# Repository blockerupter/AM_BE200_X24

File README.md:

AM_BE200_X24
============

BE200 Board with 24 chips

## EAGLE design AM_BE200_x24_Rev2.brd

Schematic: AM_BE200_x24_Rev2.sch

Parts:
C1, C17, C33, C49, C65, C81, C97, C113: 100uF; 153CLV-0605
C2, C3, C4, C5, C18, C19, C20, C21, C34, C35, C36, C37, C50, C51, C52, C53, C66, C67, C68, C69, C82, C83, C84, C85, C98, C99, C100, C101, C114, C115, C116, C117: 22uF; C1210K
C6, C7, C22, C23, C38, C39, C54, C55, C70, C71, C86, C87, C102, C103, C118, C119: 4.7uF; C0805K
C8, C24, C40, C56, C72, C88, C104, C120: 1nF; C0805K
C9, C25, C41, C57, C73, C89, C105, C121: 22nF; C0805K
C10, C26, C42, C58, C74, C90, C106, C122, C305, C306, C308, C311, C312, C313, C314, C315: 100nF; C0805K
C11, C27, C43, C59, C75, C91, C107, C123, C298: 2,2nF; C0805K
C12, C13, C14, C15, C16, C28, C29, C30, C31, C32, C44, C45, C46, C47, C48, C60, C61, C62, C63, C64, C76, C77, C78, C79, C80, C92, C93, C94, C95, C96, C108, C109, C110, C111, C112, C124, C125, C126, C127, C128: 100uF; C1210K
C129, C130, C131, C132, C134, C136, C137, C138, C139, C141, C143, C144, C145, C146, C148, C150, C151, C152, C153, C155, C157, C158, C159, C160, C162, C164, C165, C166, C167, C169, C171, C172, C173, C174, C176, C178, C179, C180, C181, C183, C185, C186, C187, C188, C190, C192, C193, C194, C195, C197, C199, C200, C201, C202, C204, C206, C207, C208, C209, C211, C213, C214, C215, C216, C218, C220, C221, C222, C223, C225, C227, C228, C229, C230, C232, C234, C235, C236, C237, C239, C241, C242, C243, C244, C246, C248, C249, C250, C251, C253, C255, C256, C257, C258, C260, C262, C263, C264, C265, C267, C269, C270, C271, C272, C274, C276, C277, C278, C279, C281, C283, C284, C285, C286, C288, C290, C291, C292, C293, C295: 100nF; MYRCL_C0603K
C133, C135, C140, C142, C147, C149, C154, C156, C161, C163, C168, C170, C175, C177, C182, C184, C189, C191, C196, C198, C203, C205, C210, C212, C217, C219, C224, C226, C231, C233, C238, C240, C245, C247, C252, C254, C259, C261, C266, C268, C273, C275, C280, C282, C287, C289, C294, C296: 4.7uF; MYRCL_C0603K
C297: 10uF; C1206K
C299, C300: 22uF; C1206K
C301, C302, C303, C304, C307: 4,7uF; C0805K
C309, C310: 22pF; C0805K
C316: 220uF; MYRCL_153CLV-0810
D1: MBR_12V; SMBJ
IC1, IC2, IC3, IC4, IC5, IC6, IC7, IC8: TPS53353_TPS53355_DQP_22; DQP22_5P479X3P24
IC9, IC10, IC11, IC12, IC13, IC14, IC15, IC16, IC17, IC18, IC19, IC20, IC21, IC22, IC23, IC24, IC25, IC26, IC27, IC28, IC29, IC30, IC31, IC32: BE200_QFN64_9X9; QFN64-9X9
IC33: AOZ1021
IC34: TLV71209DBV; SOT-23-5
IC35: TLV7; SOT-23-5
IC36: MEGA88-AU; TQFP32-08
IC37, IC38, IC39, IC40: 74HC138D; SO16
IC41: 7407D; SO14
L1, L2, L3, L4, L5, L6, L7, L8: 0.47uH; INDUCTOR_PA0513
L9: 4.7uH; INDCUCTOR_7.3X7.3
Q1: 20MHZ; OSCILLATOR_7X5_SMD
Q2: 7.37MHZ; HC49UP
R1, R9, R17, R25, R33, R41, R49, R57: 39K; R0805K
R2, R10, R18, R26, R34, R42, R50, R58: 180K; R0805K
R3, R11, R19, R27, R35, R43, R51, R59: 200K; R0805K
R4, R12, R20, R28, R36, R44, R52, R60: 100K; R0805K
R5, R13, R21, R29, R37, R45, R53, R61: 10K; R0805K
R6, R14, R22, R30, R38, R46, R54, R62: 2K49; R0805K
R7, R15, R23, R31, R39, R47, R55, R63: 56K; R0805K
R8, R16, R24, R32, R40, R48, R56, R64: 3 or 3.01; R0805K
R65, R66, R67: 7K5; R0805K
R68: 2K4; R0805K
R69, R70: 4K7; R0805K
S1: 219-05; CTS-219-05
X1, X2: MINI-FIT-JR-065.5MM; PCIE6_4.2
X3: 22-23-2031
X4, X5: XH2.54-3P
X6: AVR-ISP-6VERT; AVR-ISP-6

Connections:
0.9V: C130.1, C137.1, C144.1, C151.1, C158.1, C165.1, C172.1, C179.1, C186.1, C193.1, C200.1, C207.1, C214.1, C221.1, C228.1, C235.1, C242.1, C249.1, C256.1, C263.1, C270.1, C277.1, C284.1, C291.1, C302.2, IC9.8 (PLLDVDD), IC9.10 (PLLVDD), IC10.8 (PLLDVDD), IC10.10 (PLLVDD), IC11.8 (PLLDVDD), IC11.10 (PLLVDD), IC12.8 (PLLDVDD), IC12.10 (PLLVDD), IC13.8 (PLLDVDD), IC13.10 (PLLVDD), IC14.8 (PLLDVDD), IC14.10 (PLLVDD), IC15.8 (PLLDVDD), IC15.10 (PLLVDD), IC16.8 (PLLDVDD), IC16.10 (PLLVDD), IC17.8 (PLLDVDD), IC17.10 (PLLVDD), IC18.8 (PLLDVDD), IC18.10 (PLLVDD), IC19.8 (PLLDVDD), IC19.10 (PLLVDD), IC20.8 (PLLDVDD), IC20.10 (PLLVDD), IC21.8 (PLLDVDD), IC21.10 (PLLVDD), IC22.8 (PLLDVDD), IC22.10 (PLLVDD), IC23.8 (PLLDVDD), IC23.10 (PLLVDD), IC24.8 (PLLDVDD), IC24.10 (PLLVDD), IC25.8 (PLLDVDD), IC25.10 (PLLVDD), IC26.8 (PLLDVDD), IC26.10 (PLLVDD), IC27.8 (PLLDVDD), IC27.10 (PLLVDD), IC28.8 (PLLDVDD), IC28.10 (PLLVDD), IC29.8 (PLLDVDD), IC29.10 (PLLVDD), IC30.8 (PLLDVDD), IC30.10 (PLLVDD), IC31.8 (PLLDVDD), IC31.10 (PLLVDD), IC32.8 (PLLDVDD), IC32.10 (PLLVDD), IC34.5 (OUT)
1.8V: C129.2, C131.1, C136.2, C138.1, C143.2, C145.1, C150.2, C152.1, C157.2, C159.1, C164.2, C166.1, C171.2, C173.1, C178.2, C180.1, C185.2, C187.1, C192.2, C194.1, C199.2, C201.1, C206.2, C208.1, C213.2, C215.1, C220.2, C222.1, C227.2, C229.1, C234.2, C236.1, C241.2, C243.1, C248.2, C250.1, C255.2, C257.1, C262.2, C264.1, C269.2, C271.1, C276.2, C278.1, C283.2, C285.1, C290.2, C292.1, C304.2, IC9.5 (PLLIOVDD), IC9.6 (PLLAHVDD), IC9.25 (VDD_IO), IC9.37 (VDD_IO), IC9.56 (VDD_IO), IC10.5 (PLLIOVDD), IC10.6 (PLLAHVDD), IC10.25 (VDD_IO), IC10.37 (VDD_IO), IC10.56 (VDD_IO), IC11.5 (PLLIOVDD), IC11.6 (PLLAHVDD), IC11.25 (VDD_IO), IC11.37 (VDD_IO), IC11.56 (VDD_IO), IC12.5 (PLLIOVDD), IC12.6 (PLLAHVDD), IC12.25 (VDD_IO), IC12.37 (VDD_IO), IC12.56 (VDD_IO), IC13.5 (PLLIOVDD), IC13.6 (PLLAHVDD), IC13.25 (VDD_IO), IC13.37 (VDD_IO), IC13.56 (VDD_IO), IC14.5 (PLLIOVDD), IC14.6 (PLLAHVDD), IC14.25 (VDD_IO), IC14.37 (VDD_IO), IC14.56 (VDD_IO), IC15.5 (PLLIOVDD), IC15.6 (PLLAHVDD), IC15.25 (VDD_IO), IC15.37 (VDD_IO), IC15.56 (VDD_IO), IC16.5 (PLLIOVDD), IC16.6 (PLLAHVDD), IC16.25 (VDD_IO), IC16.37 (VDD_IO), IC16.56 (VDD_IO), IC17.5 (PLLIOVDD), IC17.6 (PLLAHVDD), IC17.25 (VDD_IO), IC17.37 (VDD_IO), IC17.56 (VDD_IO), IC18.5 (PLLIOVDD), IC18.6 (PLLAHVDD), IC18.25 (VDD_IO), IC18.37 (VDD_IO), IC18.56 (VDD_IO), IC19.5 (PLLIOVDD), IC19.6 (PLLAHVDD), IC19.25 (VDD_IO), IC19.37 (VDD_IO), IC19.56 (VDD_IO), IC20.5 (PLLIOVDD), IC20.6 (PLLAHVDD), IC20.25 (VDD_IO), IC20.37 (VDD_IO), IC20.56 (VDD_IO), IC21.5 (PLLIOVDD), IC21.6 (PLLAHVDD), IC21.25 (VDD_IO), IC21.37 (VDD_IO), IC21.56 (VDD_IO), IC22.5 (PLLIOVDD), IC22.6 (PLLAHVDD), IC22.25 (VDD_IO), IC22.37 (VDD_IO), IC22.56 (VDD_IO), IC23.5 (PLLIOVDD), IC23.6 (PLLAHVDD), IC23.25 (VDD_IO), IC23.37 (VDD_IO), IC23.56 (VDD_IO), IC24.5 (PLLIOVDD), IC24.6 (PLLAHVDD), IC24.25 (VDD_IO), IC24.37 (VDD_IO), IC24.56 (VDD_IO), IC25.5 (PLLIOVDD), IC25.6 (PLLAHVDD), IC25.25 (VDD_IO), IC25.37 (VDD_IO), IC25.56 (VDD_IO), IC26.5 (PLLIOVDD), IC26.6 (PLLAHVDD), IC26.25 (VDD_IO), IC26.37 (VDD_IO), IC26.56 (VDD_IO), IC27.5 (PLLIOVDD), IC27.6 (PLLAHVDD), IC27.25 (VDD_IO), IC27.37 (VDD_IO), IC27.56 (VDD_IO), IC28.5 (PLLIOVDD), IC28.6 (PLLAHVDD), IC28.25 (VDD_IO), IC28.37 (VDD_IO), IC28.56 (VDD_IO)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
+3V3: C299.1, C300.1, C301.2, C303.2, C305.2, C306.2, C307.2, C311.2, C312.2, C313.2, C314.2, C315.2, IC34.1 (IN), IC34.3 (EN), IC35.1 (IN), IC35.3 (EN), IC36.4 (VCC), IC36.6 (VCC), IC36.18 (AVCC), IC37.16 (VCC), IC38.6 (G1), IC38.16 (VCC), IC39.6 (G1), IC39.16 (VCC), IC40.6 (G1), IC40.16 (VCC), IC41.14 (VCC), L9.2, Q1.1 (EN), Q1.4 (VCC), R67.2, R69.2, R70.2, X6.2
+12V: C1.+, C2.1, C3.1, C4.1, C5.1, C7.1, C17.+, C18.1, C19.1, C20.1, C21.1, C23.1, C33.+, C34.1, C35.1, C36.1, C37.1, C39.1, C49.+, C50.1, C51.1, C52.1, C53.1, C55.1, C65.+, C66.1, C67.1, C68.1, C69.1, C71.1, C81.+, C82.1, C83.1, C84.1, C85.1, C87.1, C97.+, C98.1, C99.1, C100.1, C101.1, C103.1, C113.+, C114.1, C115.1, C116.1, C117.1, C119.1, C297.1, C316.+, D1.C, IC1.12 (VIN_2), IC1.13 (VIN_3), IC1.14 (VIN_4), IC1.15 (VIN_5), IC1.16 (VIN_6), IC1.17 (VIN), IC1.19 (VDD), IC2.12 (VIN_2), IC2.13 (VIN_3), IC2.14 (VIN_4), IC2.15 (VIN_5), IC2.16 (VIN_6), IC2.17 (VIN), IC2.19 (VDD), IC3.12 (VIN_2), IC3.13 (VIN_3), IC3.14 (VIN_4), IC3.15 (VIN_5), IC3.16 (VIN_6), IC3.17 (VIN), IC3.19 (VDD), IC4.12 (VIN_2), IC4.13 (VIN_3), IC4.14 (VIN_4), IC4.15 (VIN_5), IC4.16 (VIN_6), IC4.17 (VIN), IC4.19 (VDD), IC5.12 (VIN_2), IC5.13 (VIN_3), IC5.14 (VIN_4), IC5.15 (VIN_5), IC5.16 (VIN_6), IC5.17 (VIN), IC5.19 (VDD), IC6.12 (VIN_2), IC6.13 (VIN_3), IC6.14 (VIN_4), IC6.15 (VIN_5), IC6.16 (VIN_6), IC6.17 (VIN), IC6.19 (VDD), IC7.12 (VIN_2), IC7.13 (VIN_3), IC7.14 (VIN_4), IC7.15 (VIN_5), IC7.16 (VIN_6), IC7.17 (VIN), IC7.19 (VDD), IC8.12 (VIN_2), IC8.13 (VIN_3), IC8.14 (VIN_4), IC8.15 (VIN_5), IC8.16 (VIN_6), IC8.17 (VIN), IC8.19 (VDD), IC33.VIN, R3.2, R11.2, R19.2, R27.2, R35.2, R43.2, R51.2, R59.2, R65.2, X1.P1 (1), X1.P2 (2), X1.P3 (3), X2.P1 (1), X2.P2 (2), X2.P3 (3), X3.2
/CS_EN: IC36.14 (PB2(SS/OC1B/PCINT2)), IC37.4 (G2A), IC37.5 (G2B), R70.1
A0: IC36.23 (PC0(ADC0/PCINT8)), IC38.1 (A), IC39.1 (A), IC40.1 (A)
A1: IC36.24 (PC1(ADC1/PCINT9)), IC38.2 (B), IC39.2 (B), IC40.2 (B)
A2: IC36.25 (PC2(ADC2/PCINT10)), IC38.3 (C), IC39.3 (C), IC40.3 (C)
A3: IC36.26 (PC3(ADC3/PCINT11)), IC37.1 (A)
A4: IC36.27 (PC4(ADC4/SDA/PCINT12)), IC37.2 (B)
BID0: IC36.32 (PD2(INT0/PCINT18)), S1.5
BID1: IC36.1 (PD3(INT1/OC2B/PCINT19)), S1.4
BID2: IC36.2 (PD4(T0/XCK/PCINT20)), S1.3
BID3: IC36.9 (PD5(T1/OC0B/PCINT21)), S1.2
BID4: IC36.10 (PD6(AIN0/OC0A/PCINT22)), S1.1
BS: IC9.13 (BS), IC10.13 (BS), IC11.13 (BS), IC12.13 (BS), IC13.13 (BS), IC14.13 (BS), IC15.13 (BS), IC16.13 (BS), IC17.13 (BS), IC18.13 (BS), IC19.13 (BS), IC20.13 (BS), IC21.13 (BS), IC22.13 (BS), IC23.13 (BS), IC24.13 (BS), IC25.13 (BS), IC26.13 (BS), IC27.13 (BS), IC28.13 (BS), IC29.13 (BS), IC30.13 (BS), IC31.13 (BS), IC32.13 (BS), IC36.11 (PD7(AIN1/PCINT23))
CE0: IC37.15 (Y0), IC38.4 (G2A), IC38.5 (G2B)
CE1: IC37.14 (Y1), IC39.4 (G2A), IC39.5 (G2B)
CE2: IC37.13 (Y2), IC40.4 (G2A), IC40.5 (G2B)
CS0: IC9.39 (/CS_(SS)), IC38.15 (Y0)
CS1: IC10.39 (/CS_(SS)), IC38.14 (Y1)
CS2: IC11.39 (/CS_(SS)), IC38.13 (Y2)
CS3: IC12.39 (/CS_(SS)), IC38.12 (Y3)
CS4: IC13.39 (/CS_(SS)), IC38.11 (Y4)
CS5: IC14.39 (/CS_(SS)), IC38.10 (Y5)
CS6: IC15.39 (/CS_(SS)), IC38.9 (Y6)
CS7: IC16.39 (/CS_(SS)), IC38.7 (Y7)
CS8: IC17.39 (/CS_(SS)), IC39.15 (Y0)
CS9: IC18.39 (/CS_(SS)), IC39.14 (Y1)
CS10: IC19.39 (/CS_(SS)), IC39.13 (Y2)
CS11: IC20.39 (/CS_(SS)), IC39.12 (Y3)
CS12: IC21.39 (/CS_(SS)), IC39.11 (Y4)
CS13: IC22.39 (/CS_(SS)), IC39.10 (Y5)
CS14: IC23.39 (/CS_(SS)), IC39.9 (Y6)
CS15: IC24.39 (/CS_(SS)), IC39.7 (Y7)
CS16: IC25.39 (/CS_(SS)), IC40.15 (Y0)
CS17: IC26.39 (/CS_(SS)), IC40.14 (Y1)
CS18: IC27.39 (/CS_(SS)), IC40.13 (Y2)
CS19: IC28.39 (/CS_(SS)), IC40.12 (Y3)
CS20: IC29.39 (/CS_(SS)), IC40.11 (Y4)
CS21: IC30.39 (/CS_(SS)), IC40.10 (Y5)
CS22: IC31.39 (/CS_(SS)), IC40.9 (Y6)
CS23: IC32.39 (/CS_(SS)), IC40.7 (Y7)
EN_SITE1: IC1.2 (EN), R3.1, R4.2
EN_SITE2: IC2.2 (EN), R11.1, R12.2
EN_SITE3: IC3.2 (EN), R19.1, R20.2
EN_SITE4: IC4.2 (EN), R27.1, R28.2
EN_SITE5: IC5.2 (EN), R35.1, R36.2
EN_SITE6: IC6.2 (EN), R43.1, R44.2
EN_SITE7: IC7.2 (EN), R51.1, R52.2
EN_SITE8: IC8.2 (EN), R59.1, R60.2
GND: C1.-, C2.2, C3.2, C4.2, C5.2, C6.2, C7.2, C11.2, C12.2, C13.2, C14.2, C15.2, C16.2, C17.-, C18.2, C19.2, C20.2, C21.2, C22.2, C23.2, C27.2, C28.2, C29.2, C30.2, C31.2, C32.2, C33.-, C34.2, C35.2, C36.2, C37.2, C38.2, C39.2, C43.2, C44.2, C45.2, C46.2, C47.2, C48.2, C49.-, C50.2, C51.2, C52.2, C53.2, C54.2, C55.2, C59.2, C60.2, C61.2, C62.2, C63.2, C64.2, C65.-, C66.2, C67.2, C68.2, C69.2, C70.2, C71.2, C75.2, C76.2, C77.2, C78.2, C79.2, C80.2, C81.-, C82.2, C83.2, C84.2, C85.2, C86.2, C87.2, C91.2, C92.2, C93.2, C94.2, C95.2, C96.2, C97.-, C98.2, C99.2, C100.2, C101.2, C102.2, C103.2, C107.2, C108.2, C109.2, C110.2, C111.2, C112.2, C113.-, C114.2, C115.2, C116.2, C117.2, C118.2, C119.2, C123.2, C124.2, C125.2, C126.2, C127.2, C128.2, C129.1, C130.2, C131.2, C132.2, C133.2, C134.2, C135.2, C136.1, C137.2, C138.2, C139.2, C140.2, C141.2, C142.2, C143.1, C144.2, C145.2, C146.2, C147.2, C148.2, C149.2, C150.1, C151.2, C152.2, C153.2, C154.2, C155.2, C156.2, C157.1, C158.2, C159.2, C160.2, C161.2, C162.2, C163.2, C164.1, C165.2, C166.2, C167.2, C168.2, C169.2, C170.2, C171.1, C172.2, C173.2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
HARD0: IC9.43 (HARD0), IC10.43 (HARD0), IC11.43 (HARD0), IC12.43 (HARD0), IC13.43 (HARD0), IC14.43 (HARD0), IC15.43 (HARD0), IC16.43 (HARD0), IC17.43 (HARD0), IC18.43 (HARD0), IC19.43 (HARD0), IC20.43 (HARD0), IC21.43 (HARD0), IC22.43 (HARD0), IC23.43 (HARD0), IC24.43 (HARD0), IC25.43 (HARD0), IC26.43 (HARD0), IC27.43 (HARD0), IC28.43 (HARD0), IC29.43 (HARD0), IC30.43 (HARD0), IC31.43 (HARD0), IC32.43 (HARD0), IC36.12 (PB0(ICP1/CLKO/PCINT0))
HARD1: IC9.44 (HARD1), IC10.44 (HARD1), IC11.44 (HARD1), IC12.44 (HARD1), IC13.44 (HARD1), IC14.44 (HARD1), IC15.44 (HARD1), IC16.44 (HARD1), IC17.44 (HARD1), IC18.44 (HARD1), IC19.44 (HARD1), IC20.44 (HARD1), IC21.44 (HARD1), IC22.44 (HARD1), IC23.44 (HARD1), IC24.44 (HARD1), IC25.44 (HARD1), IC26.44 (HARD1), IC27.44 (HARD1), IC28.44 (HARD1), IC29.44 (HARD1), IC30.44 (HARD1), IC31.44 (HARD1), IC32.44 (HARD1), IC36.13 (PB1(OC1A/PCINT1))
MCU_RESET: IC36.29 (PC6(/RESET/PCINT14)), IC37.6 (G1), R69.1, X6.5
MISO_3.3V: IC9.41 (SO), IC10.41 (SO), IC11.41 (SO), IC12.41 (SO), IC13.41 (SO), IC14.41 (SO), IC15.41 (SO), IC16.41 (SO), IC17.41 (SO), IC18.41 (SO), IC19.41 (SO), IC20.41 (SO), IC21.41 (SO), IC22.41 (SO), IC23.41 (SO), IC24.41 (SO), IC25.41 (SO), IC26.41 (SO), IC27.41 (SO), IC28.41 (SO), IC29.41 (SO), IC30.41 (SO), IC31.41 (SO), IC32.41 (SO), IC36.16 (PB4(MISO/PCINT4)), X6.1
MOSI_3.3V: IC9.42 (SI), IC10.42 (SI), IC11.42 (SI), IC12.42 (SI), IC13.42 (SI), IC14.42 (SI), IC15.42 (SI), IC16.42 (SI), IC17.42 (SI), IC18.42 (SI), IC19.42 (SI), IC20.42 (SI), IC21.42 (SI), IC22.42 (SI), IC23.42 (SI), IC24.42 (SI), IC25.42 (SI), IC26.42 (SI), IC27.42 (SI), IC28.42 (SI), IC29.42 (SI), IC30.42 (SI), IC31.42 (SI), IC32.42 (SI), IC36.15 (PB3(MOSI/OC2A/PCINT3)), X6.4
unnamed: C10.2, IC1.6 (LL_2), IC1.7 (LL_3), IC1.8 (LL_4), IC1.9 (LL_5), IC1.10 (LL_6), IC1.11 (LL), L1.2, R7.2, R8.2
unnamed: C11.1, R8.1
unnamed: C8.1, C9.2, R7.1
unnamed: IC1.21 (TRIP), R2.2
unnamed: IC1.20 (MODE), R1.2
unnamed: C6.1, IC1.18 (VREG)
unnamed: C26.2, IC2.6 (LL_2), IC2.7 (LL_3), IC2.8 (LL_4), IC2.9 (LL_5), IC2.10 (LL_6), IC2.11 (LL), L2.2, R15.2, R16.2
unnamed: IC2.21 (TRIP), R10.2
unnamed: C10.1, IC1.4 (VBST)
unnamed: IC2.20 (MODE), R9.2
unnamed: C22.1, IC2.18 (VREG)
unnamed: C26.1, IC2.4 (VBST)
unnamed: C298.1, R66.1
unnamed: C27.1, R16.1
unnamed: C24.1, C25.2, R15.1
unnamed: IC33.LX, L9.1
unnamed: C42.2, IC3.6 (LL_2), IC3.7 (LL_3), IC3.8 (LL_4), IC3.9 (LL_5), IC3.10 (LL_6), IC3.11 (LL), L3.2, R23.2, R24.2
unnamed: IC33.FB, R67.1, R68.2
unnamed: IC33.COMP, R66.2
unnamed: IC33.EN, R65.1
unnamed: C308.2, IC36.20 (AREF)
unnamed: IC3.21 (TRIP), R18.2
unnamed: IC3.20 (MODE), R17.2
unnamed: C38.1, IC3.18 (VREG)
unnamed: C310.1, IC36.7 (PB6(XTAL1/TOSC1/PCINT6)), Q2.2
unnamed: C42.1, IC3.4 (VBST)
unnamed: C43.1, R24.1
unnamed: C309.1, IC36.8 (PB7(XTAL2/TOSC2/PCINT7)), Q2.1
unnamed: C40.1, C41.2, R23.1
unnamed: C58.2, IC4.6 (LL_2), IC4.7 (LL_3), IC4.8 (LL_4), IC4.9 (LL_5), IC4.10 (LL_6), IC4.11 (LL), L4.2, R31.2, R32.2
unnamed: IC4.21 (TRIP), R26.2
unnamed: IC4.20 (MODE), R25.2
unnamed: C54.1, IC4.18 (VREG)
unnamed: C58.1, IC4.4 (VBST)
unnamed: C59.1, R32.1
unnamed: C56.1, C57.2, R31.1
unnamed: C74.2, IC5.6 (LL_2), IC5.7 (LL_3), IC5.8 (LL_4), IC5.9 (LL_5), IC5.10 (LL_6), IC5.11 (LL), L5.2, R39.2, R40.2
unnamed: IC5.21 (TRIP), R34.2
unnamed: IC5.20 (MODE), R33.2
unnamed: C70.1, IC5.18 (VREG)
unnamed: C74.1, IC5.4 (VBST)
unnamed: C75.1, R40.1
unnamed: C72.1, C73.2, R39.1
unnamed: C90.2, IC6.6 (LL_2), IC6.7 (LL_3), IC6.8 (LL_4), IC6.9 (LL_5), IC6.10 (LL_6), IC6.11 (LL), L6.2, R47.2, R48.2
unnamed: IC6.21 (TRIP), R42.2
unnamed: IC6.20 (MODE), R41.2
unnamed: C86.1, IC6.18 (VREG)
unnamed: C90.1, IC6.4 (VBST)
unnamed: C91.1, R48.1
unnamed: C88.1, C89.2, R47.1
unnamed: C106.2, IC7.6 (LL_2), IC7.7 (LL_3), IC7.8 (LL_4), IC7.9 (LL_5), IC7.10 (LL_6), IC7.11 (LL), L7.2, R55.2, R56.2
unnamed: IC7.21 (TRIP), R50.2
unnamed: IC7.20 (MODE), R49.2
unnamed: C102.1, IC7.18 (VREG)
unnamed: C106.1, IC7.4 (VBST)
unnamed: C107.1, R56.1
unnamed: C104.1, C105.2, R55.1
unnamed: C122.2, IC8.6 (LL_2), IC8.7 (LL_3), IC8.8 (LL_4), IC8.9 (LL_5), IC8.10 (LL_6), IC8.11 (LL), L8.2, R63.2, R64.2
unnamed: IC8.21 (TRIP), R58.2
unnamed: IC8.20 (MODE), R57.2
unnamed: C118.1, IC8.18 (VREG)
unnamed: C122.1, IC8.4 (VBST)
unnamed: C123.1, R64.1
unnamed: C120.1, C121.2, R63.1
OSC_CLK: IC9.12 (OSC_CLK), IC10.12 (OSC_CLK), IC11.12 (OSC_CLK), IC12.12 (OSC_CLK), IC13.12 (OSC_CLK), IC14.12 (OSC_CLK), IC15.12 (OSC_CLK), IC16.12 (OSC_CLK), IC17.12 (OSC_CLK), IC18.12 (OSC_CLK), IC19.12 (OSC_CLK), IC20.12 (OSC_CLK), IC21.12 (OSC_CLK), IC22.12 (OSC_CLK), IC23.12 (OSC_CLK), IC24.12 (OSC_CLK), IC25.12 (OSC_CLK), IC26.12 (OSC_CLK), IC27.12 (OSC_CLK), IC28.12 (OSC_CLK), IC29.12 (OSC_CLK), IC30.12 (OSC_CLK), IC31.12 (OSC_CLK), IC32.12 (OSC_CLK), Q1.3 (OUT)
RESET: IC9.38 (RESET), IC10.38 (RESET), IC11.38 (RESET), IC12.38 (RESET), IC13.38 (RESET), IC14.38 (RESET), IC15.38 (RESET), IC16.38 (RESET), IC17.38 (RESET), IC18.38 (RESET), IC19.38 (RESET), IC20.38 (RESET), IC21.38 (RESET), IC22.38 (RESET), IC23.38 (RESET), IC24.38 (RESET), IC25.38 (RESET), IC26.38 (RESET), IC27.38 (RESET), IC28.38 (RESET), IC29.38 (RESET), IC30.38 (RESET), IC31.38 (RESET), IC32.38 (RESET), IC36.28 (PC5(ADC5/SCL/PCINT13))
RXD: IC36.30 (PD0(RXD/PCINT16)), X4.1, X5.1
SCK_3.3V: IC9.40 (SCK), IC10.40 (SCK), IC11.40 (SCK), IC12.40 (SCK), IC13.40 (SCK), IC14.40 (SCK), IC15.40 (SCK), IC16.40 (SCK), IC17.40 (SCK), IC18.40 (SCK), IC19.40 (SCK), IC20.40 (SCK), IC21.40 (SCK), IC22.40 (SCK), IC23.40 (SCK), IC24.40 (SCK), IC25.40 (SCK), IC26.40 (SCK), IC27.40 (SCK), IC28.40 (SCK), IC29.40 (SCK), IC30.40 (SCK), IC31.40 (SCK), IC32.40 (SCK), IC36.17 (PB5(SCK/PCINT5)), X6.3
TXD: IC41.2 (O), IC41.4 (O), IC41.6 (O), IC41.8 (O), IC41.10 (O), IC41.12 (O), X4.2, X5.2
TXD_MCU: IC36.31 (PD1(TXD/PCINT17)), IC41.1 (I), IC41.3 (I), IC41.5 (I), IC41.9 (I), IC41.11 (I), IC41.13 (I)
VCORE_SITE1: C9.1, C12.1, C13.1, C14.1, C15.1, C16.1, C132.1, C133.1, C134.1, C135.1, C139.1, C140.1, C141.1, C142.1, C146.1, C147.1, C148.1, C149.1, IC9.1 (VDD_CORE), IC9.2 (VDD_CORE), IC9.3 (VDD_CORE), IC9.4 (VDD_CORE), IC9.14 (VDD_CORE), IC9.15 (VDD_CORE), IC9.16 (VDD_CORE), IC9.17 (VDD_CORE), IC9.18 (VDD_CORE), IC9.19 (VDD_CORE), IC9.20 (VDD_CORE), IC9.21 (VDD_CORE), IC9.22 (VDD_CORE), IC9.23 (VDD_CORE), IC9.24 (VDD_CORE), IC9.26 (VDD_CORE), IC9.27 (VDD_CORE), IC9.28 (VDD_CORE), IC9.29 (VDD_CORE), IC9.30 (VDD_CORE), IC9.31 (VDD_CORE), IC9.32 (VDD_CORE), IC9.33 (VDD_CORE), IC9.34 (VDD_CORE), IC9.35 (VDD_CORE), IC9.36 (VDD_CORE), IC9.45 (VDD_CORE), IC9.46 (VDD_CORE), IC9.47 (VDD_CORE), IC9.48 (VDD_CORE), IC9.49 (VDD_CORE), IC9.50 (VDD_CORE), IC9.51 (VDD_CORE), IC9.52 (VDD_CORE), IC9.53 (VDD_CORE), IC9.54 (VDD_CORE), IC9.55 (VDD_CORE), IC9.57 (VDD_CORE), IC9.58 (VDD_CORE), IC9.59 (VDD_CORE), IC9.60 (VDD_CORE), IC9.61 (VDD_CORE), IC9.62 (VDD_CORE), IC9.63 (VDD_CORE), IC9.64 (VDD_CORE), IC10.1 (VDD_CORE), IC10.2 (VDD_CORE), IC10.3 (VDD_CORE), IC10.4 (VDD_CORE), IC10.14 (VDD_CORE), IC10.15 (VDD_CORE), IC10.16 (VDD_CORE), IC10.17 (VDD_CORE), IC10.18 (VDD_CORE), IC10.19 (VDD_CORE), IC10.20 (VDD_CORE), IC10.21 (VDD_CORE), IC10.22 (VDD_CORE), IC10.23 (VDD_CORE), IC10.24 (VDD_CORE), IC10.26 (VDD_CORE), IC10.27 (VDD_CORE), IC10.28 (VDD_CORE), IC10.29 (VDD_CORE), IC10.30 (VDD_CORE), IC10.31 (VDD_CORE), IC10.32 (VDD_CORE), IC10.33 (VDD_CORE), IC10.34 (VDD_CORE), IC10.35 (VDD_CORE), IC10.36 (VDD_CORE), IC10.45 (VDD_CORE), IC10.46 (VDD_CORE), IC10.47 (VDD_CORE), IC10.48 (VDD_CORE), IC10.49 (VDD_CORE), IC10.50 (VDD_CORE), IC10.51 (VDD_CORE), IC10.52 (VDD_CORE), IC10.53 (VDD_CORE), IC10.54 (VDD_CORE), IC10.55 (VDD_CORE), IC10.57 (VDD_CORE), IC10.58 (VDD_CORE), IC10.59 (VDD_CORE), IC10.60 (VDD_CORE), IC10.61 (VDD_CORE), IC10.62 (VDD_CORE), IC10.63 (VDD_CORE), IC10.64 (VDD_CORE), IC11.1 (VDD_CORE), IC11.2 (VDD_CORE), IC11.3 (VDD_CORE), IC11.4 (VDD_CORE), IC11.14 (VDD_CORE), IC11.15 (VDD_CORE), IC11.16 (VDD_CORE), IC11.17 (VDD_CORE), IC11.18 (VDD_CORE), IC11.19 (VDD_CORE), IC11.20 (VDD_CORE), IC11.21 (VDD_CORE), IC11.22 (VDD_CORE), IC11.23 (VDD_CORE), IC11.24 (VDD_CORE), IC11.26 (VDD_CORE), IC11.27 (VDD_CORE), IC11.28 (VDD_CORE), IC11.29 (VDD_CORE), IC11.30 (VDD_CORE), IC11.31 (VDD_CORE), IC11.32 (VDD_CORE), IC11.33 (VDD_CORE), IC11.34 (VDD_CORE), IC11.35 (VDD_CORE), IC11.36 (VDD_CORE), IC11.45 (VDD_CORE), IC11.46 (VDD_CORE), IC11.47 (VDD_CORE), IC11.48 (VDD_CORE), IC11.49 (VDD_CORE), IC11.50 (VDD_CORE), IC11.51 (VDD_CORE), IC11.52 (VDD_CORE), IC11.53 (VDD_CORE), IC11.54 (VDD_CORE), IC11.55 (VDD_CORE), IC11.57 (VDD_CORE), IC11.58 (VDD_CORE), IC11.59 (VDD_CORE), IC11.60 (VDD_CORE)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
VCORE_SITE2: C25.1, C28.1, C29.1, C30.1, C31.1, C32.1, C153.1, C154.1, C155.1, C156.1, C160.1, C161.1, C162.1, C163.1, C167.1, C168.1, C169.1, C170.1, IC12.1 (VDD_CORE), IC12.2 (VDD_CORE), IC12.3 (VDD_CORE), IC12.4 (VDD_CORE), IC12.14 (VDD_CORE), IC12.15 (VDD_CORE), IC12.16 (VDD_CORE), IC12.17 (VDD_CORE), IC12.18 (VDD_CORE), IC12.19 (VDD_CORE), IC12.20 (VDD_CORE), IC12.21 (VDD_CORE), IC12.22 (VDD_CORE), IC12.23 (VDD_CORE), IC12.24 (VDD_CORE), IC12.26 (VDD_CORE), IC12.27 (VDD_CORE), IC12.28 (VDD_CORE), IC12.29 (VDD_CORE), IC12.30 (VDD_CORE), IC12.31 (VDD_CORE), IC12.32 (VDD_CORE), IC12.33 (VDD_CORE), IC12.34 (VDD_CORE), IC12.35 (VDD_CORE), IC12.36 (VDD_CORE), IC12.45 (VDD_CORE), IC12.46 (VDD_CORE), IC12.47 (VDD_CORE), IC12.48 (VDD_CORE), IC12.49 (VDD_CORE), IC12.50 (VDD_CORE), IC12.51 (VDD_CORE), IC12.52 (VDD_CORE), IC12.53 (VDD_CORE), IC12.54 (VDD_CORE), IC12.55 (VDD_CORE), IC12.57 (VDD_CORE), IC12.58 (VDD_CORE), IC12.59 (VDD_CORE), IC12.60 (VDD_CORE), IC12.61 (VDD_CORE), IC12.62 (VDD_CORE), IC12.63 (VDD_CORE), IC12.64 (VDD_CORE), IC13.1 (VDD_CORE), IC13.2 (VDD_CORE), IC13.3 (VDD_CORE), IC13.4 (VDD_CORE), IC13.14 (VDD_CORE), IC13.15 (VDD_CORE), IC13.16 (VDD_CORE), IC13.17 (VDD_CORE), IC13.18 (VDD_CORE), IC13.19 (VDD_CORE), IC13.20 (VDD_CORE), IC13.21 (VDD_CORE), IC13.22 (VDD_CORE), IC13.23 (VDD_CORE), IC13.24 (VDD_CORE), IC13.26 (VDD_CORE), IC13.27 (VDD_CORE), IC13.28 (VDD_CORE), IC13.29 (VDD_CORE), IC13.30 (VDD_CORE), IC13.31 (VDD_CORE), IC13.32 (VDD_CORE), IC13.33 (VDD_CORE), IC13.34 (VDD_CORE), IC13.35 (VDD_CORE), IC13.36 (VDD_CORE), IC13.45 (VDD_CORE), IC13.46 (VDD_CORE), IC13.47 (VDD_CORE), IC13.48 (VDD_CORE), IC13.49 (VDD_CORE), IC13.50 (VDD_CORE), IC13.51 (VDD_CORE), IC13.52 (VDD_CORE), IC13.53 (VDD_CORE), IC13.54 (VDD_CORE), IC13.55 (VDD_CORE), IC13.57 (VDD_CORE), IC13.58 (VDD_CORE), IC13.59 (VDD_CORE), IC13.60 (VDD_CORE), IC13.61 (VDD_CORE), IC13.62 (VDD_CORE), IC13.63 (VDD_CORE), IC13.64 (VDD_CORE), IC14.1 (VDD_CORE), IC14.2 (VDD_CORE), IC14.3 (VDD_CORE), IC14.4 (VDD_CORE), IC14.14 (VDD_CORE), IC14.15 (VDD_CORE), IC14.16 (VDD_CORE), IC14.17 (VDD_CORE), IC14.18 (VDD_CORE), IC14.19 (VDD_CORE), IC14.20 (VDD_CORE), IC14.21 (VDD_CORE), IC14.22 (VDD_CORE), IC14.23 (VDD_CORE), IC14.24 (VDD_CORE), IC14.26 (VDD_CORE), IC14.27 (VDD_CORE), IC14.28 (VDD_CORE), IC14.29 (VDD_CORE), IC14.30 (VDD_CORE), IC14.31 (VDD_CORE), IC14.32 (VDD_CORE), IC14.33 (VDD_CORE), IC14.34 (VDD_CORE), IC14.35 (VDD_CORE), IC14.36 (VDD_CORE), IC14.45 (VDD_CORE), IC14.46 (VDD_CORE), IC14.47 (VDD_CORE), IC14.48 (VDD_CORE), IC14.49 (VDD_CORE), IC14.50 (VDD_CORE), IC14.51 (VDD_CORE), IC14.52 (VDD_CORE), IC14.53 (VDD_CORE), IC14.54 (VDD_CORE), IC14.55 (VDD_CORE), IC14.57 (VDD_CORE), IC14.58 (VDD_CORE), IC14.59 (VDD_CORE), IC14.60 (VDD_CORE)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
VCORE_SITE3: C41.1, C44.1, C45.1, C46.1, C47.1, C48.1, C174.1, C175.1, C176.1, C177.1, C181.1, C182.1, C183.1, C184.1, C188.1, C189.1, C190.1, C191.1, IC15.1 (VDD_CORE), IC15.2 (VDD_CORE), IC15.3 (VDD_CORE), IC15.4 (VDD_CORE), IC15.14 (VDD_CORE), IC15.15 (VDD_CORE), IC15.16 (VDD_CORE), IC15.17 (VDD_CORE), IC15.18 (VDD_CORE), IC15.19 (VDD_CORE), IC15.20 (VDD_CORE), IC15.21 (VDD_CORE), IC15.22 (VDD_CORE), IC15.23 (VDD_CORE), IC15.24 (VDD_CORE), IC15.26 (VDD_CORE), IC15.27 (VDD_CORE), IC15.28 (VDD_CORE), IC15.29 (VDD_CORE), IC15.30 (VDD_CORE), IC15.31 (VDD_CORE), IC15.32 (VDD_CORE), IC15.33 (VDD_CORE), IC15.34 (VDD_CORE), IC15.35 (VDD_CORE), IC15.36 (VDD_CORE), IC15.45 (VDD_CORE), IC15.46 (VDD_CORE), IC15.47 (VDD_CORE), IC15.48 (VDD_CORE), IC15.49 (VDD_CORE), IC15.50 (VDD_CORE), IC15.51 (VDD_CORE), IC15.52 (VDD_CORE), IC15.53 (VDD_CORE), IC15.54 (VDD_CORE), IC15.55 (VDD_CORE), IC15.57 (VDD_CORE), IC15.58 (VDD_CORE), IC15.59 (VDD_CORE), IC15.60 (VDD_CORE), IC15.61 (VDD_CORE), IC15.62 (VDD_CORE), IC15.63 (VDD_CORE), IC15.64 (VDD_CORE), IC16.1 (VDD_CORE), IC16.2 (VDD_CORE), IC16.3 (VDD_CORE), IC16.4 (VDD_CORE), IC16.14 (VDD_CORE), IC16.15 (VDD_CORE), IC16.16 (VDD_CORE), IC16.17 (VDD_CORE), IC16.18 (VDD_CORE), IC16.19 (VDD_CORE), IC16.20 (VDD_CORE), IC16.21 (VDD_CORE), IC16.22 (VDD_CORE), IC16.23 (VDD_CORE), IC16.24 (VDD_CORE), IC16.26 (VDD_CORE), IC16.27 (VDD_CORE), IC16.28 (VDD_CORE), IC16.29 (VDD_CORE), IC16.30 (VDD_CORE), IC16.31 (VDD_CORE), IC16.32 (VDD_CORE), IC16.33 (VDD_CORE), IC16.34 (VDD_CORE), IC16.35 (VDD_CORE), IC16.36 (VDD_CORE), IC16.45 (VDD_CORE), IC16.46 (VDD_CORE), IC16.47 (VDD_CORE), IC16.48 (VDD_CORE), IC16.49 (VDD_CORE), IC16.50 (VDD_CORE), IC16.51 (VDD_CORE), IC16.52 (VDD_CORE), IC16.53 (VDD_CORE), IC16.54 (VDD_CORE), IC16.55 (VDD_CORE), IC16.57 (VDD_CORE), IC16.58 (VDD_CORE), IC16.59 (VDD_CORE), IC16.60 (VDD_CORE), IC16.61 (VDD_CORE), IC16.62 (VDD_CORE), IC16.63 (VDD_CORE), IC16.64 (VDD_CORE), IC17.1 (VDD_CORE), IC17.2 (VDD_CORE), IC17.3 (VDD_CORE), IC17.4 (VDD_CORE), IC17.14 (VDD_CORE), IC17.15 (VDD_CORE), IC17.16 (VDD_CORE), IC17.17 (VDD_CORE), IC17.18 (VDD_CORE), IC17.19 (VDD_CORE), IC17.20 (VDD_CORE), IC17.21 (VDD_CORE), IC17.22 (VDD_CORE), IC17.23 (VDD_CORE), IC17.24 (VDD_CORE), IC17.26 (VDD_CORE), IC17.27 (VDD_CORE), IC17.28 (VDD_CORE), IC17.29 (VDD_CORE), IC17.30 (VDD_CORE), IC17.31 (VDD_CORE), IC17.32 (VDD_CORE), IC17.33 (VDD_CORE), IC17.34 (VDD_CORE), IC17.35 (VDD_CORE), IC17.36 (VDD_CORE), IC17.45 (VDD_CORE), IC17.46 (VDD_CORE), IC17.47 (VDD_CORE), IC17.48 (VDD_CORE), IC17.49 (VDD_CORE), IC17.50 (VDD_CORE), IC17.51 (VDD_CORE), IC17.52 (VDD_CORE), IC17.53 (VDD_CORE), IC17.54 (VDD_CORE), IC17.55 (VDD_CORE), IC17.57 (VDD_CORE), IC17.58 (VDD_CORE), IC17.59 (VDD_CORE), IC17.60 (VDD_CORE)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
VCORE_SITE4: C57.1, C60.1, C61.1, C62.1, C63.1, C64.1, C195.1, C196.1, C197.1, C198.1, C202.1, C203.1, C204.1, C205.1, C209.1, C210.1, C211.1, C212.1, IC18.1 (VDD_CORE), IC18.2 (VDD_CORE), IC18.3 (VDD_CORE), IC18.4 (VDD_CORE), IC18.14 (VDD_CORE), IC18.15 (VDD_CORE), IC18.16 (VDD_CORE), IC18.17 (VDD_CORE), IC18.18 (VDD_CORE), IC18.19 (VDD_CORE), IC18.20 (VDD_CORE), IC18.21 (VDD_CORE), IC18.22 (VDD_CORE), IC18.23 (VDD_CORE), IC18.24 (VDD_CORE), IC18.26 (VDD_CORE), IC18.27 (VDD_CORE), IC18.28 (VDD_CORE), IC18.29 (VDD_CORE), IC18.30 (VDD_CORE), IC18.31 (VDD_CORE), IC18.32 (VDD_CORE), IC18.33 (VDD_CORE), IC18.34 (VDD_CORE), IC18.35 (VDD_CORE), IC18.36 (VDD_CORE), IC18.45 (VDD_CORE), IC18.46 (VDD_CORE), IC18.47 (VDD_CORE), IC18.48 (VDD_CORE), IC18.49 (VDD_CORE), IC18.50 (VDD_CORE), IC18.51 (VDD_CORE), IC18.52 (VDD_CORE), IC18.53 (VDD_CORE), IC18.54 (VDD_CORE), IC18.55 (VDD_CORE), IC18.57 (VDD_CORE), IC18.58 (VDD_CORE), IC18.59 (VDD_CORE), IC18.60 (VDD_CORE), IC18.61 (VDD_CORE), IC18.62 (VDD_CORE), IC18.63 (VDD_CORE), IC18.64 (VDD_CORE), IC19.1 (VDD_CORE), IC19.2 (VDD_CORE), IC19.3 (VDD_CORE), IC19.4 (VDD_CORE), IC19.14 (VDD_CORE), IC19.15 (VDD_CORE), IC19.16 (VDD_CORE), IC19.17 (VDD_CORE), IC19.18 (VDD_CORE), IC19.19 (VDD_CORE), IC19.20 (VDD_CORE), IC19.21 (VDD_CORE), IC19.22 (VDD_CORE), IC19.23 (VDD_CORE), IC19.24 (VDD_CORE), IC19.26 (VDD_CORE), IC19.27 (VDD_CORE), IC19.28 (VDD_CORE), IC19.29 (VDD_CORE), IC19.30 (VDD_CORE), IC19.31 (VDD_CORE), IC19.32 (VDD_CORE), IC19.33 (VDD_CORE), IC19.34 (VDD_CORE), IC19.35 (VDD_CORE), IC19.36 (VDD_CORE), IC19.45 (VDD_CORE), IC19.46 (VDD_CORE), IC19.47 (VDD_CORE), IC19.48 (VDD_CORE), IC19.49 (VDD_CORE), IC19.50 (VDD_CORE), IC19.51 (VDD_CORE), IC19.52 (VDD_CORE), IC19.53 (VDD_CORE), IC19.54 (VDD_CORE), IC19.55 (VDD_CORE), IC19.57 (VDD_CORE), IC19.58 (VDD_CORE), IC19.59 (VDD_CORE), IC19.60 (VDD_CORE), IC19.61 (VDD_CORE), IC19.62 (VDD_CORE), IC19.63 (VDD_CORE), IC19.64 (VDD_CORE), IC20.1 (VDD_CORE), IC20.2 (VDD_CORE), IC20.3 (VDD_CORE), IC20.4 (VDD_CORE), IC20.14 (VDD_CORE), IC20.15 (VDD_CORE), IC20.16 (VDD_CORE), IC20.17 (VDD_CORE), IC20.18 (VDD_CORE), IC20.19 (VDD_CORE), IC20.20 (VDD_CORE), IC20.21 (VDD_CORE), IC20.22 (VDD_CORE), IC20.23 (VDD_CORE), IC20.24 (VDD_CORE), IC20.26 (VDD_CORE), IC20.27 (VDD_CORE), IC20.28 (VDD_CORE), IC20.29 (VDD_CORE), IC20.30 (VDD_CORE), IC20.31 (VDD_CORE), IC20.32 (VDD_CORE), IC20.33 (VDD_CORE), IC20.34 (VDD_CORE), IC20.35 (VDD_CORE), IC20.36 (VDD_CORE), IC20.45 (VDD_CORE), IC20.46 (VDD_CORE), IC20.47 (VDD_CORE), IC20.48 (VDD_CORE), IC20.49 (VDD_CORE), IC20.50 (VDD_CORE), IC20.51 (VDD_CORE), IC20.52 (VDD_CORE), IC20.53 (VDD_CORE), IC20.54 (VDD_CORE), IC20.55 (VDD_CORE), IC20.57 (VDD_CORE), IC20.58 (VDD_CORE), IC20.59 (VDD_CORE), IC20.60 (VDD_CORE)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
VCORE_SITE5: C73.1, C76.1, C77.1, C78.1, C79.1, C80.1, C216.1, C217.1, C218.1, C219.1, C223.1, C224.1, C225.1, C226.1, C230.1, C231.1, C232.1, C233.1, IC21.1 (VDD_CORE), IC21.2 (VDD_CORE), IC21.3 (VDD_CORE), IC21.4 (VDD_CORE), IC21.14 (VDD_CORE), IC21.15 (VDD_CORE), IC21.16 (VDD_CORE), IC21.17 (VDD_CORE), IC21.18 (VDD_CORE), IC21.19 (VDD_CORE), IC21.20 (VDD_CORE), IC21.21 (VDD_CORE), IC21.22 (VDD_CORE), IC21.23 (VDD_CORE), IC21.24 (VDD_CORE), IC21.26 (VDD_CORE), IC21.27 (VDD_CORE), IC21.28 (VDD_CORE), IC21.29 (VDD_CORE), IC21.30 (VDD_CORE), IC21.31 (VDD_CORE), IC21.32 (VDD_CORE), IC21.33 (VDD_CORE), IC21.34 (VDD_CORE), IC21.35 (VDD_CORE), IC21.36 (VDD_CORE), IC21.45 (VDD_CORE), IC21.46 (VDD_CORE), IC21.47 (VDD_CORE), IC21.48 (VDD_CORE), IC21.49 (VDD_CORE), IC21.50 (VDD_CORE), IC21.51 (VDD_CORE), IC21.52 (VDD_CORE), IC21.53 (VDD_CORE), IC21.54 (VDD_CORE), IC21.55 (VDD_CORE), IC21.57 (VDD_CORE), IC21.58 (VDD_CORE), IC21.59 (VDD_CORE), IC21.60 (VDD_CORE), IC21.61 (VDD_CORE), IC21.62 (VDD_CORE), IC21.63 (VDD_CORE), IC21.64 (VDD_CORE), IC22.1 (VDD_CORE), IC22.2 (VDD_CORE), IC22.3 (VDD_CORE), IC22.4 (VDD_CORE), IC22.14 (VDD_CORE), IC22.15 (VDD_CORE), IC22.16 (VDD_CORE), IC22.17 (VDD_CORE), IC22.18 (VDD_CORE), IC22.19 (VDD_CORE), IC22.20 (VDD_CORE), IC22.21 (VDD_CORE), IC22.22 (VDD_CORE), IC22.23 (VDD_CORE), IC22.24 (VDD_CORE), IC22.26 (VDD_CORE), IC22.27 (VDD_CORE), IC22.28 (VDD_CORE), IC22.29 (VDD_CORE), IC22.30 (VDD_CORE), IC22.31 (VDD_CORE), IC22.32 (VDD_CORE), IC22.33 (VDD_CORE), IC22.34 (VDD_CORE), IC22.35 (VDD_CORE), IC22.36 (VDD_CORE), IC22.45 (VDD_CORE), IC22.46 (VDD_CORE), IC22.47 (VDD_CORE), IC22.48 (VDD_CORE), IC22.49 (VDD_CORE), IC22.50 (VDD_CORE), IC22.51 (VDD_CORE), IC22.52 (VDD_CORE), IC22.53 (VDD_CORE), IC22.54 (VDD_CORE), IC22.55 (VDD_CORE), IC22.57 (VDD_CORE), IC22.58 (VDD_CORE), IC22.59 (VDD_CORE), IC22.60 (VDD_CORE), IC22.61 (VDD_CORE), IC22.62 (VDD_CORE), IC22.63 (VDD_CORE), IC22.64 (VDD_CORE), IC23.1 (VDD_CORE), IC23.2 (VDD_CORE), IC23.3 (VDD_CORE), IC23.4 (VDD_CORE), IC23.14 (VDD_CORE), IC23.15 (VDD_CORE), IC23.16 (VDD_CORE), IC23.17 (VDD_CORE), IC23.18 (VDD_CORE), IC23.19 (VDD_CORE), IC23.20 (VDD_CORE), IC23.21 (VDD_CORE), IC23.22 (VDD_CORE), IC23.23 (VDD_CORE), IC23.24 (VDD_CORE), IC23.26 (VDD_CORE), IC23.27 (VDD_CORE), IC23.28 (VDD_CORE), IC23.29 (VDD_CORE), IC23.30 (VDD_CORE), IC23.31 (VDD_CORE), IC23.32 (VDD_CORE), IC23.33 (VDD_CORE), IC23.34 (VDD_CORE), IC23.35 (VDD_CORE), IC23.36 (VDD_CORE), IC23.45 (VDD_CORE), IC23.46 (VDD_CORE), IC23.47 (VDD_CORE), IC23.48 (VDD_CORE), IC23.49 (VDD_CORE), IC23.50 (VDD_CORE), IC23.51 (VDD_CORE), IC23.52 (VDD_CORE), IC23.53 (VDD_CORE), IC23.54 (VDD_CORE), IC23.55 (VDD_CORE), IC23.57 (VDD_CORE), IC23.58 (VDD_CORE), IC23.59 (VDD_CORE), IC23.60 (VDD_CORE)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
VCORE_SITE6: C89.1, C92.1, C93.1, C94.1, C95.1, C96.1, C237.1, C238.1, C239.1, C240.1, C244.1, C245.1, C246.1, C247.1, C251.1, C252.1, C253.1, C254.1, IC24.1 (VDD_CORE), IC24.2 (VDD_CORE), IC24.3 (VDD_CORE), IC24.4 (VDD_CORE), IC24.14 (VDD_CORE), IC24.15 (VDD_CORE), IC24.16 (VDD_CORE), IC24.17 (VDD_CORE), IC24.18 (VDD_CORE), IC24.19 (VDD_CORE), IC24.20 (VDD_CORE), IC24.21 (VDD_CORE), IC24.22 (VDD_CORE), IC24.23 (VDD_CORE), IC24.24 (VDD_CORE), IC24.26 (VDD_CORE), IC24.27 (VDD_CORE), IC24.28 (VDD_CORE), IC24.29 (VDD_CORE), IC24.30 (VDD_CORE), IC24.31 (VDD_CORE), IC24.32 (VDD_CORE), IC24.33 (VDD_CORE), IC24.34 (VDD_CORE), IC24.35 (VDD_CORE), IC24.36 (VDD_CORE), IC24.45 (VDD_CORE), IC24.46 (VDD_CORE), IC24.47 (VDD_CORE), IC24.48 (VDD_CORE), IC24.49 (VDD_CORE), IC24.50 (VDD_CORE), IC24.51 (VDD_CORE), IC24.52 (VDD_CORE), IC24.53 (VDD_CORE), IC24.54 (VDD_CORE), IC24.55 (VDD_CORE), IC24.57 (VDD_CORE), IC24.58 (VDD_CORE), IC24.59 (VDD_CORE), IC24.60 (VDD_CORE), IC24.61 (VDD_CORE), IC24.62 (VDD_CORE), IC24.63 (VDD_CORE), IC24.64 (VDD_CORE), IC25.1 (VDD_CORE), IC25.2 (VDD_CORE), IC25.3 (VDD_CORE), IC25.4 (VDD_CORE), IC25.14 (VDD_CORE), IC25.15 (VDD_CORE), IC25.16 (VDD_CORE), IC25.17 (VDD_CORE), IC25.18 (VDD_CORE), IC25.19 (VDD_CORE), IC25.20 (VDD_CORE), IC25.21 (VDD_CORE), IC25.22 (VDD_CORE), IC25.23 (VDD_CORE), IC25.24 (VDD_CORE), IC25.26 (VDD_CORE), IC25.27 (VDD_CORE), IC25.28 (VDD_CORE), IC25.29 (VDD_CORE), IC25.30 (VDD_CORE), IC25.31 (VDD_CORE), IC25.32 (VDD_CORE), IC25.33 (VDD_CORE), IC25.34 (VDD_CORE), IC25.35 (VDD_CORE), IC25.36 (VDD_CORE), IC25.45 (VDD_CORE), IC25.46 (VDD_CORE), IC25.47 (VDD_CORE), IC25.48 (VDD_CORE), IC25.49 (VDD_CORE), IC25.50 (VDD_CORE), IC25.51 (VDD_CORE), IC25.52 (VDD_CORE), IC25.53 (VDD_CORE), IC25.54 (VDD_CORE), IC25.55 (VDD_CORE), IC25.57 (VDD_CORE), IC25.58 (VDD_CORE), IC25.59 (VDD_CORE), IC25.60 (VDD_CORE), IC25.61 (VDD_CORE), IC25.62 (VDD_CORE), IC25.63 (VDD_CORE), IC25.64 (VDD_CORE), IC26.1 (VDD_CORE), IC26.2 (VDD_CORE), IC26.3 (VDD_CORE), IC26.4 (VDD_CORE), IC26.14 (VDD_CORE), IC26.15 (VDD_CORE), IC26.16 (VDD_CORE), IC26.17 (VDD_CORE), IC26.18 (VDD_CORE), IC26.19 (VDD_CORE), IC26.20 (VDD_CORE), IC26.21 (VDD_CORE), IC26.22 (VDD_CORE), IC26.23 (VDD_CORE), IC26.24 (VDD_CORE), IC26.26 (VDD_CORE), IC26.27 (VDD_CORE), IC26.28 (VDD_CORE), IC26.29 (VDD_CORE), IC26.30 (VDD_CORE), IC26.31 (VDD_CORE), IC26.32 (VDD_CORE), IC26.33 (VDD_CORE), IC26.34 (VDD_CORE), IC26.35 (VDD_CORE), IC26.36 (VDD_CORE), IC26.45 (VDD_CORE), IC26.46 (VDD_CORE), IC26.47 (VDD_CORE), IC26.48 (VDD_CORE), IC26.49 (VDD_CORE), IC26.50 (VDD_CORE), IC26.51 (VDD_CORE), IC26.52 (VDD_CORE), IC26.53 (VDD_CORE), IC26.54 (VDD_CORE), IC26.55 (VDD_CORE), IC26.57 (VDD_CORE), IC26.58 (VDD_CORE), IC26.59 (VDD_CORE), IC26.60 (VDD_CORE)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
VCORE_SITE7: C105.1, C108.1, C109.1, C110.1, C111.1, C112.1, C258.1, C259.1, C260.1, C261.1, C265.1, C266.1, C267.1, C268.1, C272.1, C273.1, C274.1, C275.1, IC27.1 (VDD_CORE), IC27.2 (VDD_CORE), IC27.3 (VDD_CORE), IC27.4 (VDD_CORE), IC27.14 (VDD_CORE), IC27.15 (VDD_CORE), IC27.16 (VDD_CORE), IC27.17 (VDD_CORE), IC27.18 (VDD_CORE), IC27.19 (VDD_CORE), IC27.20 (VDD_CORE), IC27.21 (VDD_CORE), IC27.22 (VDD_CORE), IC27.23 (VDD_CORE), IC27.24 (VDD_CORE), IC27.26 (VDD_CORE), IC27.27 (VDD_CORE), IC27.28 (VDD_CORE), IC27.29 (VDD_CORE), IC27.30 (VDD_CORE), IC27.31 (VDD_CORE), IC27.32 (VDD_CORE), IC27.33 (VDD_CORE), IC27.34 (VDD_CORE), IC27.35 (VDD_CORE), IC27.36 (VDD_CORE), IC27.45 (VDD_CORE), IC27.46 (VDD_CORE), IC27.47 (VDD_CORE), IC27.48 (VDD_CORE), IC27.49 (VDD_CORE), IC27.50 (VDD_CORE), IC27.51 (VDD_CORE), IC27.52 (VDD_CORE), IC27.53 (VDD_CORE), IC27.54 (VDD_CORE), IC27.55 (VDD_CORE), IC27.57 (VDD_CORE), IC27.58 (VDD_CORE), IC27.59 (VDD_CORE), IC27.60 (VDD_CORE), IC27.61 (VDD_CORE), IC27.62 (VDD_CORE), IC27.63 (VDD_CORE), IC27.64 (VDD_CORE), IC28.1 (VDD_CORE), IC28.2 (VDD_CORE), IC28.3 (VDD_CORE), IC28.4 (VDD_CORE), IC28.14 (VDD_CORE), IC28.15 (VDD_CORE), IC28.16 (VDD_CORE), IC28.17 (VDD_CORE), IC28.18 (VDD_CORE), IC28.19 (VDD_CORE), IC28.20 (VDD_CORE), IC28.21 (VDD_CORE), IC28.22 (VDD_CORE), IC28.23 (VDD_CORE), IC28.24 (VDD_CORE), IC28.26 (VDD_CORE), IC28.27 (VDD_CORE), IC28.28 (VDD_CORE), IC28.29 (VDD_CORE), IC28.30 (VDD_CORE), IC28.31 (VDD_CORE), IC28.32 (VDD_CORE), IC28.33 (VDD_CORE), IC28.34 (VDD_CORE), IC28.35 (VDD_CORE), IC28.36 (VDD_CORE), IC28.45 (VDD_CORE), IC28.46 (VDD_CORE), IC28.47 (VDD_CORE), IC28.48 (VDD_CORE), IC28.49 (VDD_CORE), IC28.50 (VDD_CORE), IC28.51 (VDD_CORE), IC28.52 (VDD_CORE), IC28.53 (VDD_CORE), IC28.54 (VDD_CORE), IC28.55 (VDD_CORE), IC28.57 (VDD_CORE), IC28.58 (VDD_CORE), IC28.59 (VDD_CORE), IC28.60 (VDD_CORE), IC28.61 (VDD_CORE), IC28.62 (VDD_CORE), IC28.63 (VDD_CORE), IC28.64 (VDD_CORE), IC29.1 (VDD_CORE), IC29.2 (VDD_CORE), IC29.3 (VDD_CORE), IC29.4 (VDD_CORE), IC29.14 (VDD_CORE), IC29.15 (VDD_CORE), IC29.16 (VDD_CORE), IC29.17 (VDD_CORE), IC29.18 (VDD_CORE), IC29.19 (VDD_CORE), IC29.20 (VDD_CORE), IC29.21 (VDD_CORE), IC29.22 (VDD_CORE), IC29.23 (VDD_CORE), IC29.24 (VDD_CORE), IC29.26 (VDD_CORE), IC29.27 (VDD_CORE), IC29.28 (VDD_CORE), IC29.29 (VDD_CORE), IC29.30 (VDD_CORE), IC29.31 (VDD_CORE), IC29.32 (VDD_CORE), IC29.33 (VDD_CORE), IC29.34 (VDD_CORE), IC29.35 (VDD_CORE), IC29.36 (VDD_CORE), IC29.45 (VDD_CORE), IC29.46 (VDD_CORE), IC29.47 (VDD_CORE), IC29.48 (VDD_CORE), IC29.49 (VDD_CORE), IC29.50 (VDD_CORE), IC29.51 (VDD_CORE), IC29.52 (VDD_CORE), IC29.53 (VDD_CORE), IC29.54 (VDD_CORE), IC29.55 (VDD_CORE), IC29.57 (VDD_CORE), IC29.58 (VDD_CORE), IC29.59 (VDD_CORE), IC29.60 (VDD_CORE)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
VCORE_SITE8: C121.1, C124.1, C125.1, C126.1, C127.1, C128.1, C279.1, C280.1, C281.1, C282.1, C286.1, C287.1, C288.1, C289.1, C293.1, C294.1, C295.1, C296.1, IC30.1 (VDD_CORE), IC30.2 (VDD_CORE), IC30.3 (VDD_CORE), IC30.4 (VDD_CORE), IC30.14 (VDD_CORE), IC30.15 (VDD_CORE), IC30.16 (VDD_CORE), IC30.17 (VDD_CORE), IC30.18 (VDD_CORE), IC30.19 (VDD_CORE), IC30.20 (VDD_CORE), IC30.21 (VDD_CORE), IC30.22 (VDD_CORE), IC30.23 (VDD_CORE), IC30.24 (VDD_CORE), IC30.26 (VDD_CORE), IC30.27 (VDD_CORE), IC30.28 (VDD_CORE), IC30.29 (VDD_CORE), IC30.30 (VDD_CORE), IC30.31 (VDD_CORE), IC30.32 (VDD_CORE), IC30.33 (VDD_CORE), IC30.34 (VDD_CORE), IC30.35 (VDD_CORE), IC30.36 (VDD_CORE), IC30.45 (VDD_CORE), IC30.46 (VDD_CORE), IC30.47 (VDD_CORE), IC30.48 (VDD_CORE), IC30.49 (VDD_CORE), IC30.50 (VDD_CORE), IC30.51 (VDD_CORE), IC30.52 (VDD_CORE), IC30.53 (VDD_CORE), IC30.54 (VDD_CORE), IC30.55 (VDD_CORE), IC30.57 (VDD_CORE), IC30.58 (VDD_CORE), IC30.59 (VDD_CORE), IC30.60 (VDD_CORE), IC30.61 (VDD_CORE), IC30.62 (VDD_CORE), IC30.63 (VDD_CORE), IC30.64 (VDD_CORE), IC31.1 (VDD_CORE), IC31.2 (VDD_CORE), IC31.3 (VDD_CORE), IC31.4 (VDD_CORE), IC31.14 (VDD_CORE), IC31.15 (VDD_CORE), IC31.16 (VDD_CORE), IC31.17 (VDD_CORE), IC31.18 (VDD_CORE), IC31.19 (VDD_CORE), IC31.20 (VDD_CORE), IC31.21 (VDD_CORE), IC31.22 (VDD_CORE), IC31.23 (VDD_CORE), IC31.24 (VDD_CORE), IC31.26 (VDD_CORE), IC31.27 (VDD_CORE), IC31.28 (VDD_CORE), IC31.29 (VDD_CORE), IC31.30 (VDD_CORE), IC31.31 (VDD_CORE), IC31.32 (VDD_CORE), IC31.33 (VDD_CORE), IC31.34 (VDD_CORE), IC31.35 (VDD_CORE), IC31.36 (VDD_CORE), IC31.45 (VDD_CORE), IC31.46 (VDD_CORE), IC31.47 (VDD_CORE), IC31.48 (VDD_CORE), IC31.49 (VDD_CORE), IC31.50 (VDD_CORE), IC31.51 (VDD_CORE), IC31.52 (VDD_CORE), IC31.53 (VDD_CORE), IC31.54 (VDD_CORE), IC31.55 (VDD_CORE), IC31.57 (VDD_CORE), IC31.58 (VDD_CORE), IC31.59 (VDD_CORE), IC31.60 (VDD_CORE), IC31.61 (VDD_CORE), IC31.62 (VDD_CORE), IC31.63 (VDD_CORE), IC31.64 (VDD_CORE), IC32.1 (VDD_CORE), IC32.2 (VDD_CORE), IC32.3 (VDD_CORE), IC32.4 (VDD_CORE), IC32.14 (VDD_CORE), IC32.15 (VDD_CORE), IC32.16 (VDD_CORE), IC32.17 (VDD_CORE), IC32.18 (VDD_CORE), IC32.19 (VDD_CORE), IC32.20 (VDD_CORE), IC32.21 (VDD_CORE), IC32.22 (VDD_CORE), IC32.23 (VDD_CORE), IC32.24 (VDD_CORE), IC32.26 (VDD_CORE), IC32.27 (VDD_CORE), IC32.28 (VDD_CORE), IC32.29 (VDD_CORE), IC32.30 (VDD_CORE), IC32.31 (VDD_CORE), IC32.32 (VDD_CORE), IC32.33 (VDD_CORE), IC32.34 (VDD_CORE), IC32.35 (VDD_CORE), IC32.36 (VDD_CORE), IC32.45 (VDD_CORE), IC32.46 (VDD_CORE), IC32.47 (VDD_CORE), IC32.48 (VDD_CORE), IC32.49 (VDD_CORE), IC32.50 (VDD_CORE), IC32.51 (VDD_CORE), IC32.52 (VDD_CORE), IC32.53 (VDD_CORE), IC32.54 (VDD_CORE), IC32.55 (VDD_CORE), IC32.57 (VDD_CORE), IC32.58 (VDD_CORE), IC32.59 (VDD_CORE), IC32.60 (VDD_CORE)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
VFB_SITE1: C8.2, IC1.1 (VFB), R5.2, R6.1
VFB_SITE2: C24.2, IC2.1 (VFB), R13.2, R14.1
VFB_SITE3: C40.2, IC3.1 (VFB), R21.2, R22.1
VFB_SITE4: C56.2, IC4.1 (VFB), R29.2, R30.1
VFB_SITE5: C72.2, IC5.1 (VFB), R37.2, R38.1
VFB_SITE6: C88.2, IC6.1 (VFB), R45.2, R46.1
VFB_SITE7: C104.2, IC7.1 (VFB), R53.2, R54.1
VFB_SITE8: C120.2, IC8.1 (VFB), R61.2, R62.1

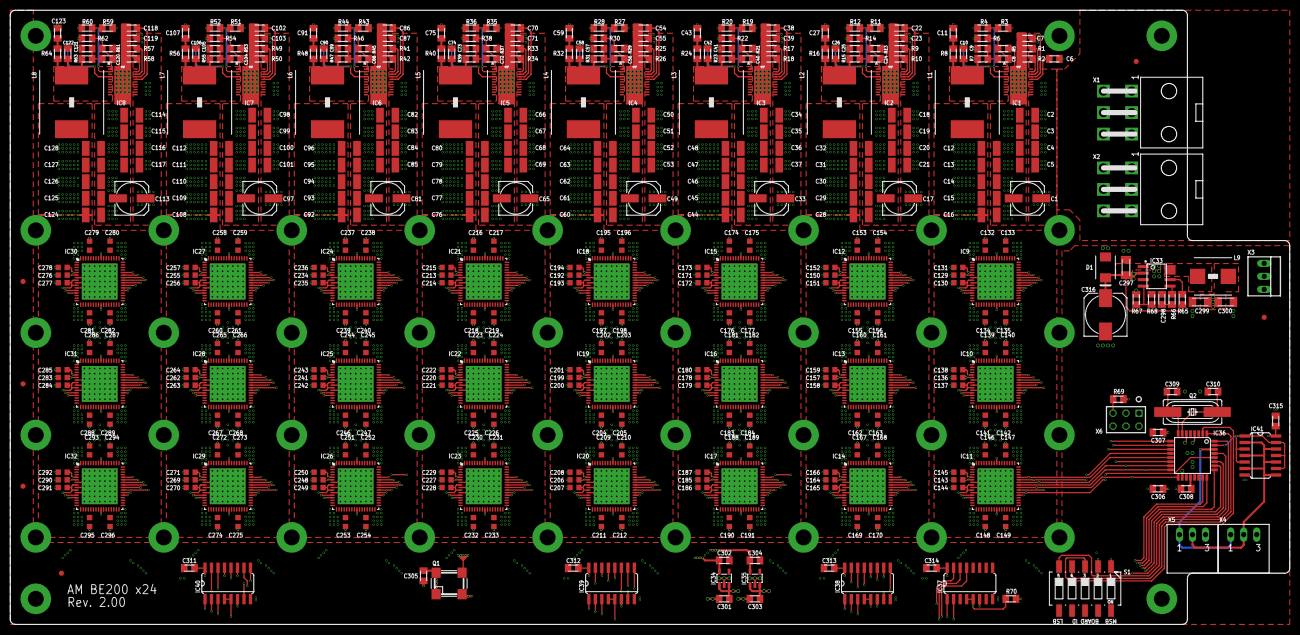
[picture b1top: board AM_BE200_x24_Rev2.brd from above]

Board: 6 copper layers, 250.0 x 120.0 mm, 452 parts (0 on the bottom side), 143 nets.

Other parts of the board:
U$1, U$2, U$3, U$4, U$5, U$6: MARKER-ROUND-1X3

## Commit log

2014-06-06 add README
2014-06-06 remove temp file
2014-06-06 Rev2 24-Chip Board
2014-06-14 Add BOM
2014-06-27 Increase VDD_CORE to 0.8V
